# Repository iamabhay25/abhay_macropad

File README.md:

<div align="center">

# Abhay's Macropad

### Custom 9-Key Macropad

Custom designed macropad for everyday use.

Features 9 keys with per-key underglow LEDs, a 128×32 SSD1306 OLED display, and a rotary encoder.

<br><br>

<br><br>

| ⚡ RP2040 MC | ⌨️ 9 Keys | ✨ Underlit Keys | 📺 .91" OLED Screen | 🎛️ 1 Rotary Encoder |
|:--:|:--:|:--:|:--:|:--:|

</div>

<br><br><br><br>

<div align="center">

### Sponsored By

<br>

</div>

<br><br><br><br><br>

<div align="center">

### Bill of Materials

<br>

<div align="center">

| Qty | Component | Cost |
|:---:|-----------|------|
| 4x | [M2.5 Self-Tapping Screws](https://www.aliexpress.us/item/3256805544601650.html) | $1.97 |
| 4x | [M3 Heat-Set Inserts](https://www.aliexpress.us/item/3256808480358197.html) | $1.99 |
| 4x | [M3 Machine Screws](https://www.aliexpress.us/item/2255800784679048.html) | $1.87 |
| 1x | [Seeed Studio XIAO RP2040](https://www.aliexpress.us/item/3256807240972277.html) | $11.73 |
| 1x | [SSD1306 128×32 OLED Display](https://www.aliexpress.us/item/3256805115814136.html) | $2.39 |
| 9x | [Tactile Switches](https://www.aliexpress.us/item/3256808352947766.html) | $3.51 |
| 9x | [Blank White Keycaps](https://www.aliexpress.us/item/3256809017491500.html) | $3.25 |
| 9x | [SOD-123 Diodes](https://www.aliexpress.us/item/3256805388348871.html) | $1.53 |
| 3x | [1206 Capacitors](https://www.aliexpress.us/item/3256807177349573.html) | $1.27 |
| 1x | [0805 Resistor](https://www.aliexpress.us/item/3256809618872827.html) | $1.42 |
| 1x | [Bus Buffer Gate](https://www.aliexpress.us/item/3256807066238250.html) | $1.51 |
| 1x | [Soldering Wire](https://www.aliexpress.us/item/3256806675545472.html) | $1.41 |
| 1x | [Custom PCB](https://jlcpcb.com/) | $3.30 |
| 1x | 3D Printed Case (Printing Legion) | $0.00 |

<br>

**Parts Subtotal:** $35.16

**Fees:** $4.01

**Tax:** $2.96

**Printing Legion Shipping:** $7.00

**Grand Total:** $49.13

<br><br><br><br><br>

<div align="left">
  
### PCB Schematic

<br>

<br><br>

### PCB Layout

<br>

<div align="center">

**Top Layer**

<br>

<br><br>

**Bottom Layer**

<br>

<br><br>

**3D View**

<br>

<br><br>

</div>

<br><br>

### Case Design

<br>

<div align="center">

**Top Case**

<br>

<br><br>

**Bottom Case**

<br>

</div>

<br><br>

### Final Assembly

<br>

<div align="center">

</div>

<br><br>

<div align="center">

*Designed and Built by Abhay P.*

</div>

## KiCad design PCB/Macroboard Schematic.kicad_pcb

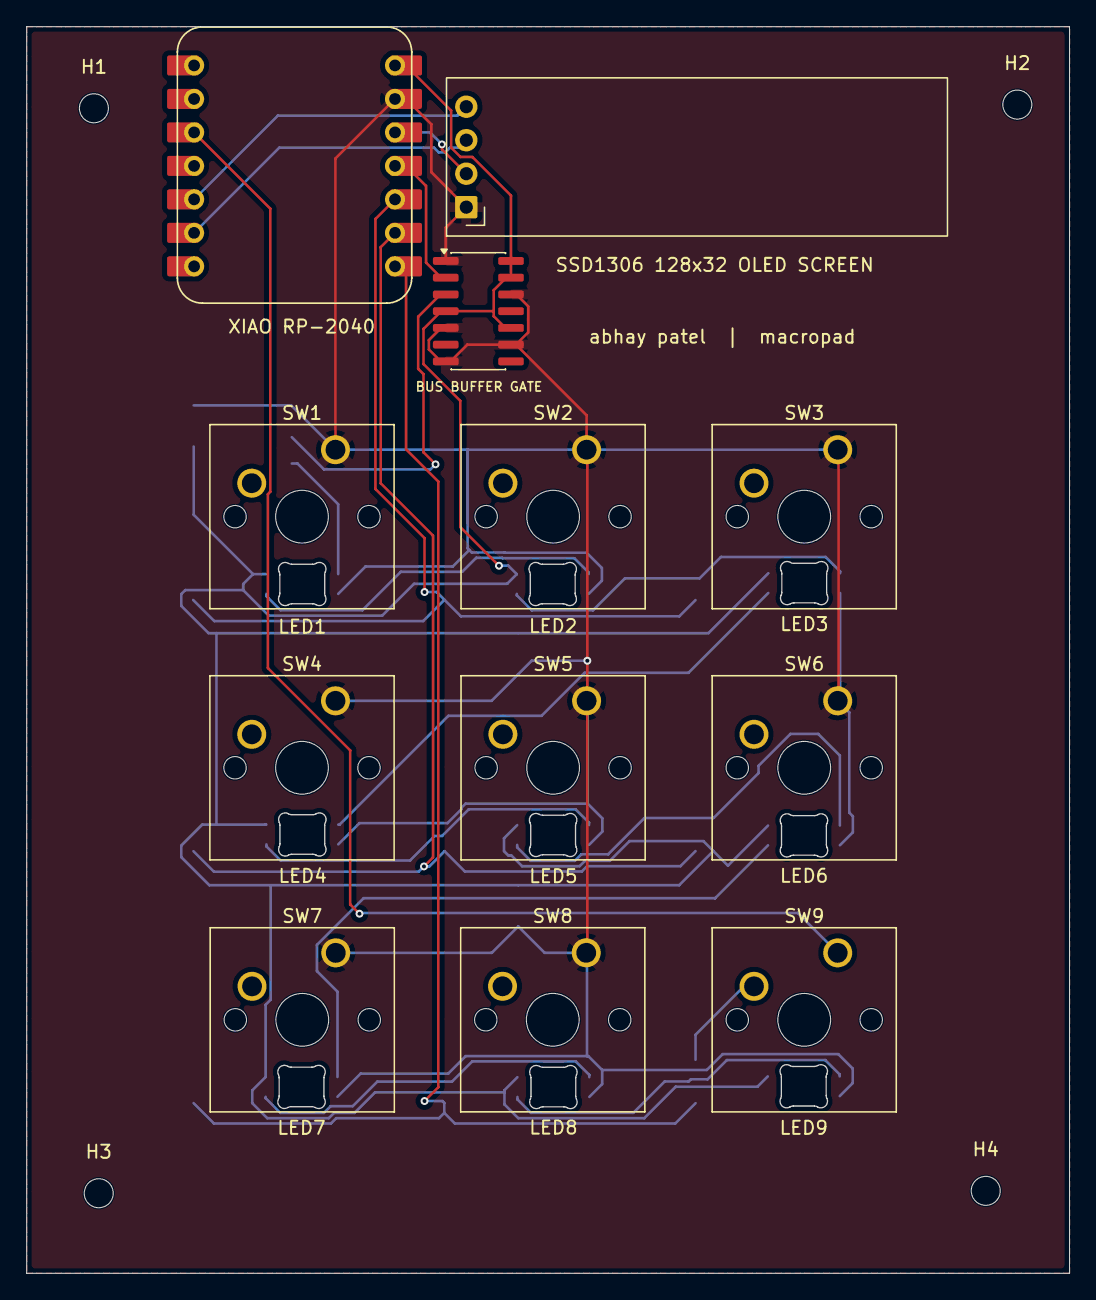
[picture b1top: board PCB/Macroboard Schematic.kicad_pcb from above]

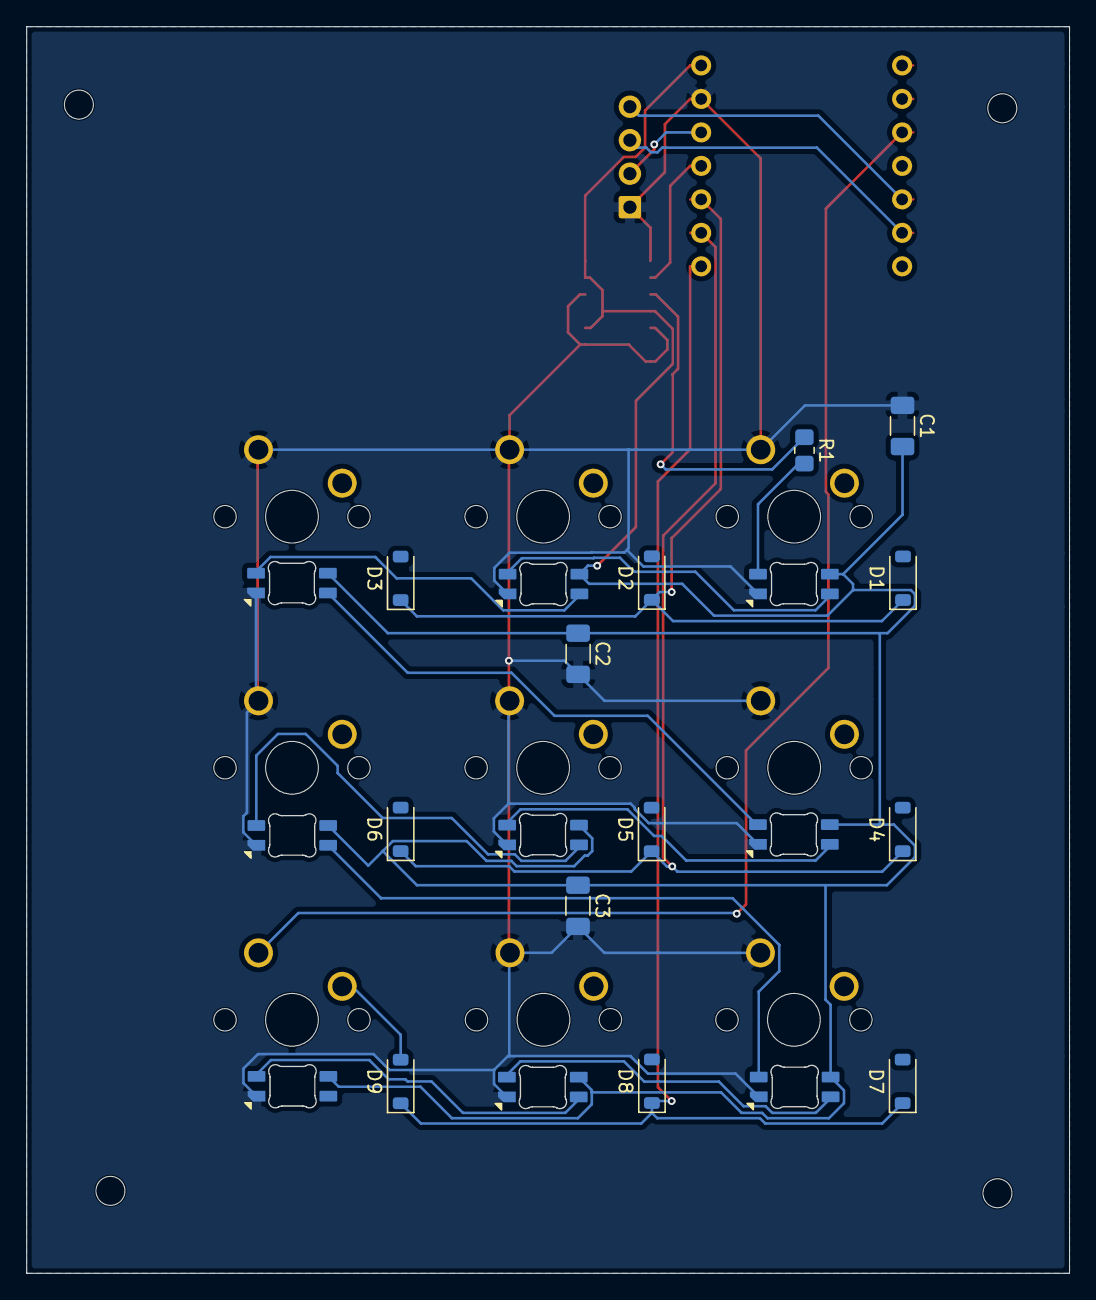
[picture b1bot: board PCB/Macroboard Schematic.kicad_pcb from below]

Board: 2 copper layers, 79.1 x 94.6 mm, 38 parts (22 on the bottom side), 21 nets.

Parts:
BUS BUFFER GATE: 74AHCT125; SOIC-14_3.9x8.7mm_P1.27mm
C1, C2, C3: 100nF; C_1206_3216Metric_Pad1.33x1.80mm_HandSolder
D1, D2, D3, D4, D5, D6, D7, D8, D9: 1N4148W; D_SOD-123
H1, H2, H3, H4: MountingHole; MountingHole_2.2mm_M2
LED1, LED2, LED3, LED4, LED5, LED6, LED7, LED8, LED9: MX_SK6812MINI-E; LED_MX_6028R
R1: 330R; R_0805_2012Metric_Pad1.20x1.40mm_HandSolder
SSD1306 128x32 OLED SCREEN: ER_OLEDM0.91_1x-I2C
SW1, SW2, SW3, SW4, SW5, SW6, SW7, SW8, SW9: SW_Push; SW_Cherry_MX_1.00u_PCB
U3: XIAO-RP2040-DIP

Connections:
+3.3V: SSD1306 128x32 OLED SCREEN.2 (VCC), U3.12 (3V3)
+5V: BUS BUFFER GATE.4, BUS BUFFER GATE.10, BUS BUFFER GATE.13, BUS BUFFER GATE.14 (VCC), C1.2, C2.1, C3.1, LED1.1 (VDD), LED2.1 (VDD), LED3.1 (VDD), LED4.1 (VDD), LED5.1 (VDD), LED6.1 (VDD), LED7.1 (VDD), LED8.1 (VDD), LED9.1 (VDD), U3.14 (VBUS)
COLUMN 3: SW9.1, U3.3 (P28_A2_D2)
GND: BUS BUFFER GATE.1, BUS BUFFER GATE.5, BUS BUFFER GATE.7 (GND), BUS BUFFER GATE.9, BUS BUFFER GATE.12, C1.1, C2.2, C3.2, LED1.3 (VSS), LED2.3 (VSS), LED3.3 (VSS), LED4.3 (VSS), LED5.3 (VSS), LED6.3 (VSS), LED7.3 (VSS), LED8.3 (VSS), LED9.3 (VSS), SSD1306 128x32 OLED SCREEN.1 (GND), SW1.1, SW2.1, SW3.1, SW4.1, SW5.1, SW6.1, SW7.1, SW8.1, U3.13 (GND)
LED: BUS BUFFER GATE.2, U3.11 (P3_D10_MOSI)
unnamed: D9.2 (A), SW9.2
unnamed: LED1.4 (DIN), R1.2
unnamed: LED1.2 (DOUT), LED2.4 (DIN)
unnamed: LED2.2 (DOUT), LED3.4 (DIN)
unnamed: LED3.2 (DOUT), LED4.4 (DIN)
unnamed: LED4.2 (DOUT), LED5.4 (DIN)
unnamed: LED5.2 (DOUT), LED6.4 (DIN)
unnamed: LED6.2 (DOUT), LED7.4 (DIN)
unnamed: LED7.2 (DOUT), LED8.4 (DIN)
unnamed: LED8.2 (DOUT), LED9.4 (DIN)
unnamed: BUS BUFFER GATE.3, R1.1
ROW 1: D1.1 (K), D2.1 (K), D3.1 (K), U3.10 (P4_D9_MISO)
ROW 2: D4.1 (K), D5.1 (K), D6.1 (K), U3.9 (P2_D8_SCK)
ROW 3: D7.1 (K), D8.1 (K), D9.1 (K), U3.8 (P1_D7_RX)
SCL: SSD1306 128x32 OLED SCREEN.3 (SCL), U3.6 (P7_SCL_D5)
SDA: SSD1306 128x32 OLED SCREEN.4 (SDA), U3.5 (P6_SDA_D4)

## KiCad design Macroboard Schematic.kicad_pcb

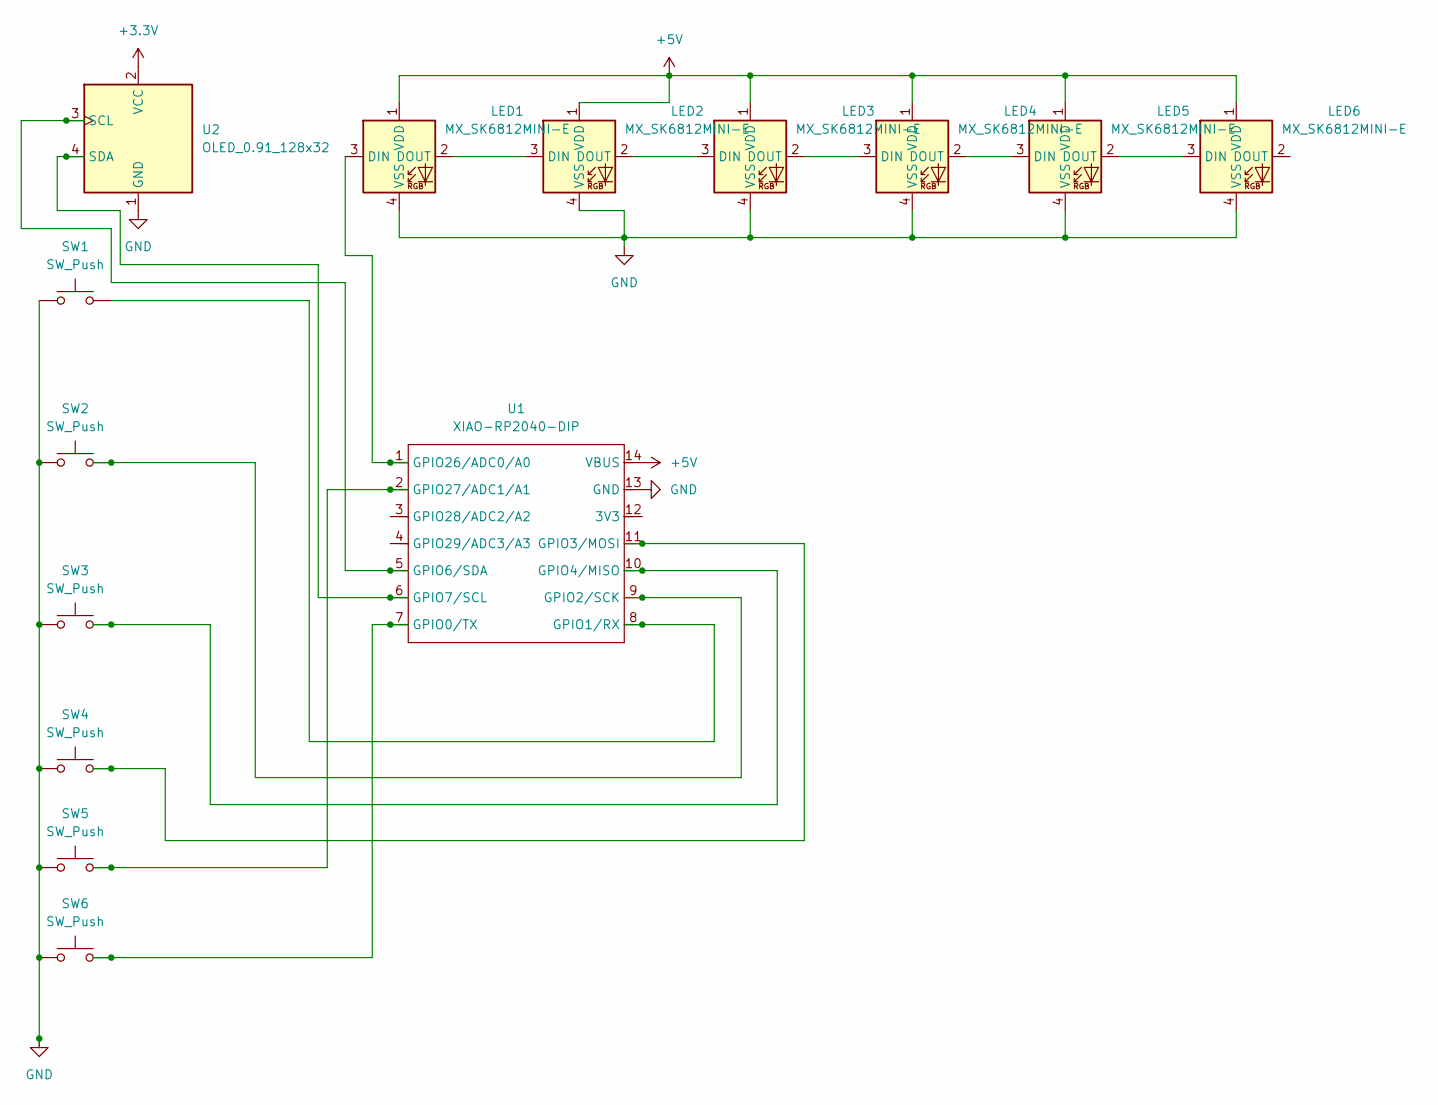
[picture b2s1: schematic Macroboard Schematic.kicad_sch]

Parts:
LED1, LED2, LED3, LED4, LED5, LED6: MX_SK6812MINI-E; LED_SK6812MINI-E_3.2x2.8mm_P1.5mm_ReverseMount
SW1, SW2, SW3, SW4, SW5, SW6: SW_Push; SW_Cherry_MX_1.00u_PCB
U1: XIAO-RP2040-DIP
U2: OLED_0.91_128x32

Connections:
+3.3V: U2.2 (VCC)
+5V: LED1.1 (VDD), LED2.1 (VDD), LED3.1 (VDD), LED4.1 (VDD), LED5.1 (VDD), LED6.1 (VDD), U1.14 (VBUS)
GND: LED1.4 (VSS), LED2.4 (VSS), LED3.4 (VSS), LED4.4 (VSS), LED5.4 (VSS), LED6.4 (VSS), SW1.1, SW2.1, SW3.1, SW4.1, SW5.1, SW6.1, U1.13 (GND), U2.1 (GND)
unnamed: LED1.3 (DIN), U1.1 (GPIO26/ADC0/A0)
unnamed: LED1.2 (DOUT), LED2.3 (DIN)
unnamed: LED2.2 (DOUT), LED3.3 (DIN)
unnamed: LED3.2 (DOUT), LED4.3 (DIN)
unnamed: LED4.2 (DOUT), LED5.3 (DIN)
unnamed: LED5.2 (DOUT), LED6.3 (DIN)
unnamed: SW6.2, U1.7 (GPIO0/TX)
unnamed: SW1.2, U1.8 (GPIO1/RX)
unnamed: SW2.2, U1.9 (GPIO2/SCK)
unnamed: SW4.2, U1.11 (GPIO3/MOSI)
unnamed: SW3.2, U1.10 (GPIO4/MISO)
unnamed: U1.5 (GPIO6/SDA), U2.3 (SCL)
unnamed: U1.6 (GPIO7/SCL), U2.4 (SDA)
unnamed: SW5.2, U1.2 (GPIO27/ADC1/A1)

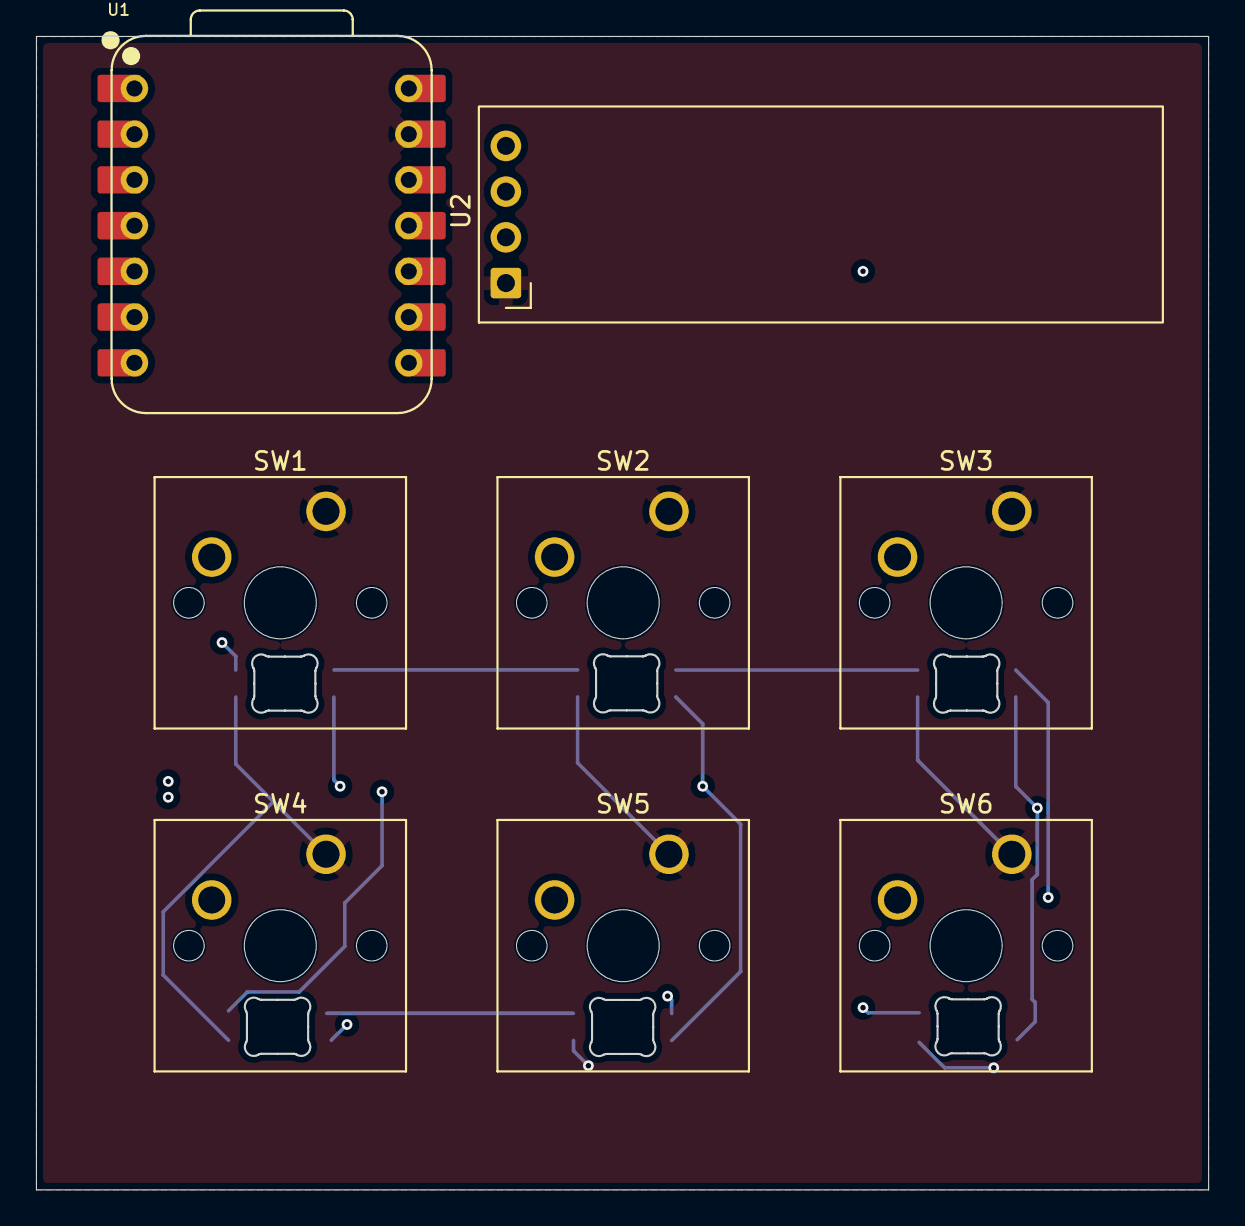
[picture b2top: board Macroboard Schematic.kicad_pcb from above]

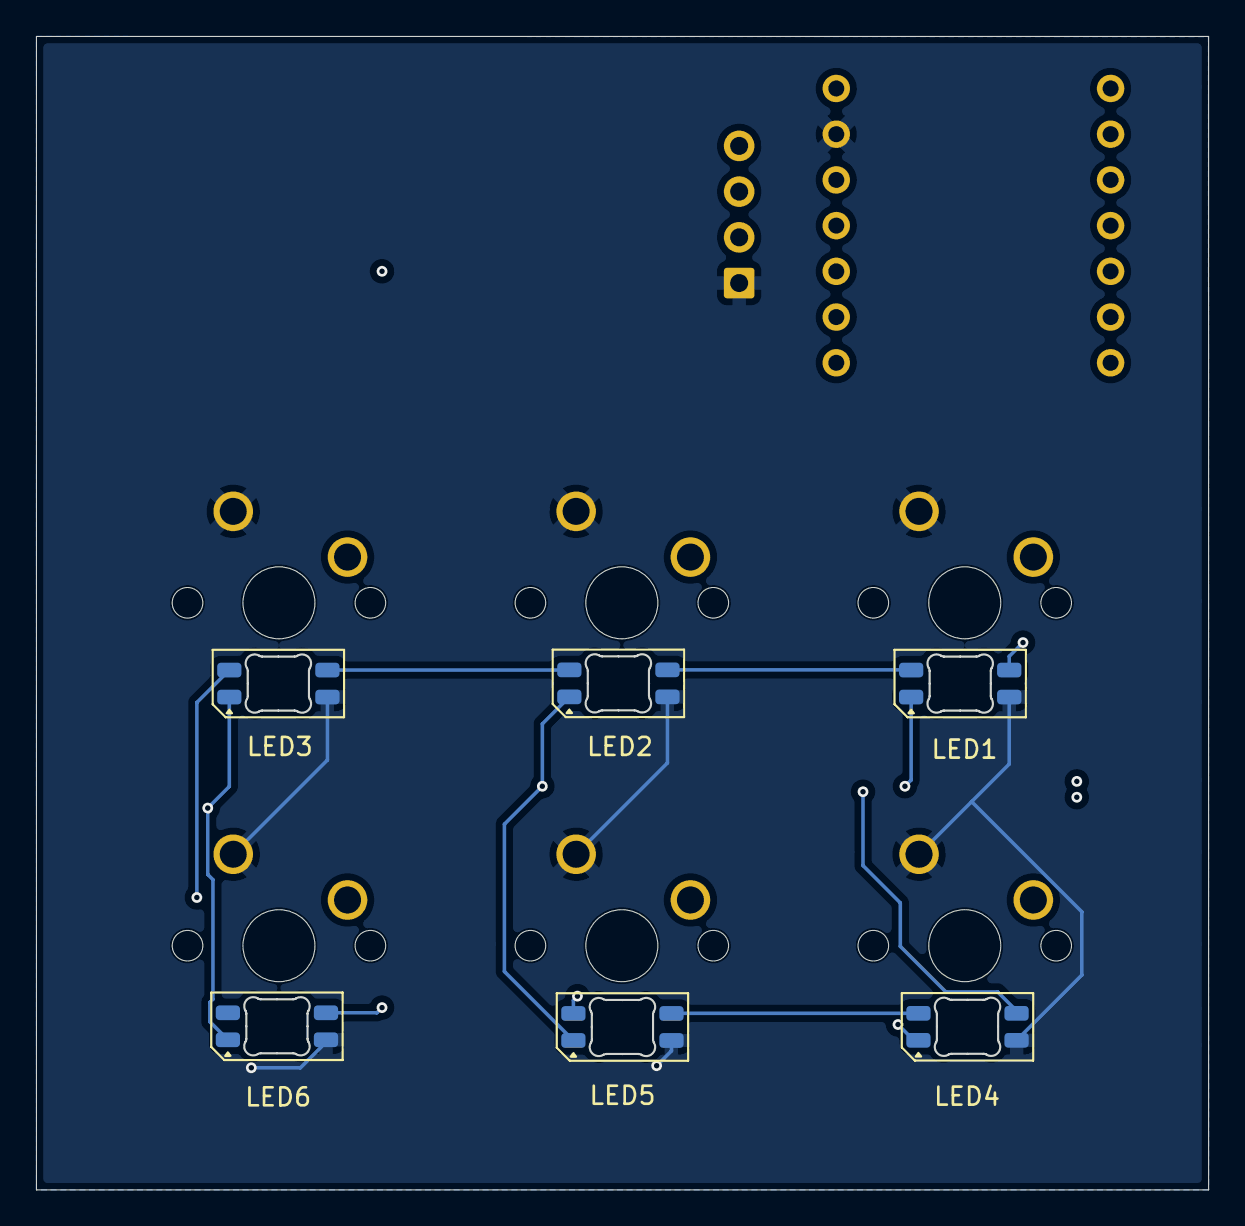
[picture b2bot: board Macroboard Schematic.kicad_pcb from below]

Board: 4 copper layers, 65.1 x 64.1 mm, 14 parts (6 on the bottom side), 16 nets.

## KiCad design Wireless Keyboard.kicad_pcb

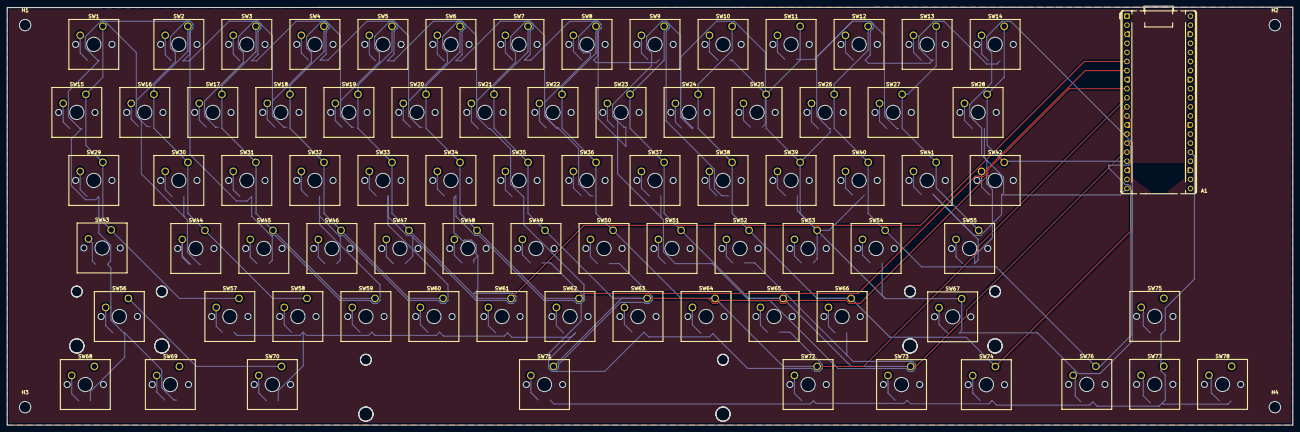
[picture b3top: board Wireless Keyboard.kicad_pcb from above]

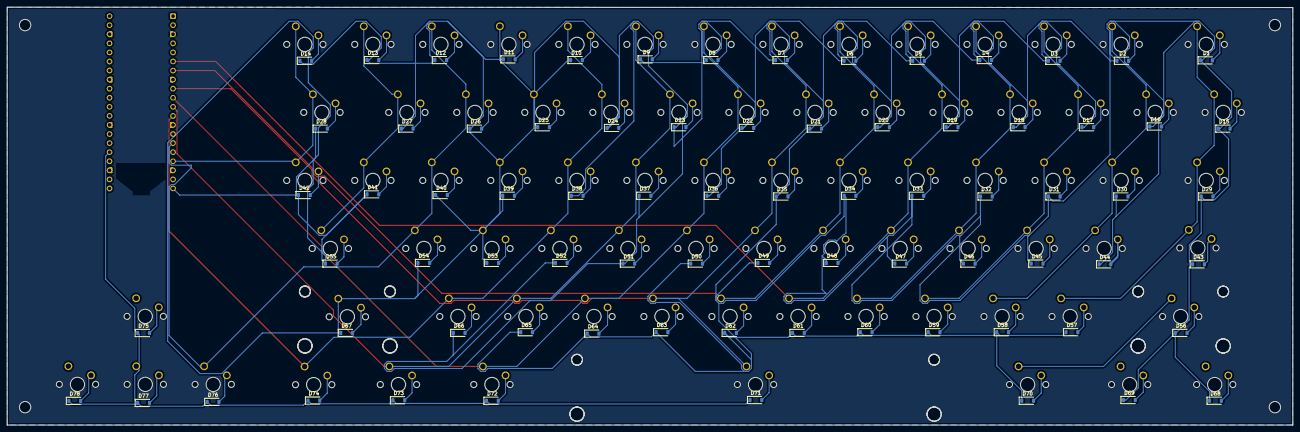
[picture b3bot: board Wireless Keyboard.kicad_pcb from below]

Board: 4 copper layers, 360.0 x 117.0 mm, 164 parts (78 on the bottom side), 93 nets.

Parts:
A1: SC0918; RaspberryPi_Pico_Common_THT
D1, D2, D3, D4, D5, D6, D7, D8, D9, D10, D11, D12, D13, D14, D15, D16, D17, D18, D19, D20, D21, D22, D23, D24, D25, D26, D27, D28, D29, D30, D31, D32, D33, D34, D35, D36, D37, D38, D39, D40, D41, D42, D43, D44, D45, D46, D47, D48, D49, D50, D51, D52, D53, D54, D55, D56, D57, D58, D59, D60, D61, D62, D63, D64, D65, D66, D67, D68, D69, D70, D71, D72, D73, D74, D75, D76, D77, D78: D; D_SOD-123
H1, H2, H3, H4: MountingHole; MountingHole_3.2mm_M3
S3, S4: MX_stab; STAB_MX_2.25u
S5: MX_stab; STAB_MX_6.25u
SW1, SW28, SW29, SW72: SW_Push; SW_Cherry_MX_1.50u_PCB
SW2, SW3, SW4, SW5, SW6, SW7, SW8, SW9, SW10, SW11, SW12, SW13, SW14, SW15, SW16, SW17, SW18, SW19, SW20, SW21, SW22, SW23, SW24, SW25, SW26, SW27, SW30, SW31, SW32, SW33, SW34, SW35, SW36, SW37, SW38, SW39, SW40, SW41, SW42, SW44, SW45, SW46, SW47, SW48, SW49, SW50, SW51, SW52, SW53, SW54, SW57, SW58, SW59, SW60, SW61, SW62, SW63, SW64, SW65, SW66, SW75, SW76, SW77, SW78: SW_Push; SW_Cherry_MX_1.00u_PCB
SW43, SW55, SW70: SW_Push; SW_Cherry_MX_1.75u_PCB
SW56, SW67: SW_Push; SW_Cherry_MX_2.25u_PCB
SW68, SW69, SW73, SW74: SW_Push; SW_Cherry_MX_1.25u_PCB
SW71: SW_Push; SW_Cherry_MX_6.25u_PCB

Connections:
/column 1: A1.1 (GP0), SW1.1, SW15.1, SW29.1, SW43.1, SW57.1
/column 2: A1.2 (GP1), SW2.1, SW16.1, SW30.1, SW44.1, SW58.1
/column 3: A1.4 (GP2), SW3.1, SW17.1, SW31.1, SW45.1, SW59.1
/column 4: A1.5 (GP3), SW4.1, SW18.1, SW32.1, SW46.1, SW60.1
/column 5: A1.6 (GP4), SW5.1, SW19.1, SW33.1, SW47.1, SW61.1
/column 6: A1.7 (GP5), SW6.1, SW20.1, SW34.1, SW48.1, SW62.1
/column 7: A1.9 (GP6), SW7.1, SW21.1, SW35.1, SW49.1, SW63.1, SW71.1
/column 8: A1.10 (GP7), SW8.1, SW22.1, SW36.1, SW50.1, SW64.1, SW72.1
/column 9: A1.11 (GP8), SW9.1, SW23.1, SW37.1, SW51.1, SW65.1, SW73.1
/column 10: A1.12 (GP9), SW10.1, SW24.1, SW38.1, SW52.1, SW66.1, SW74.1
/column 11: A1.14 (GP10), A1.19 (GP14), A1.20 (GP15), A1.21 (GP16), A1.22 (GP17), A1.24 (GP18), D1.1 (K), D2.1 (K), D3.1 (K), D4.1 (K), D5.1 (K), D6.1 (K), D7.1 (K), D8.1 (K), D9.1 (K), D10.1 (K), D11.1 (K), D12.1 (K), D13.1 (K), D14.1 (K), D15.1 (K), D16.1 (K), D17.1 (K), D18.1 (K), D19.1 (K), D20.1 (K), D21.1 (K), D22.1 (K), D23.1 (K), D24.1 (K), D25.1 (K), D26.1 (K), D27.1 (K), D28.1 (K), D29.1 (K), D30.1 (K), D31.1 (K), D32.1 (K), D33.1 (K), D34.1 (K), D35.1 (K), D36.1 (K), D37.1 (K), D38.1 (K), D39.1 (K), D40.1 (K), D41.1 (K), D42.1 (K), D43.1 (K), D44.1 (K), D45.1 (K), D46.1 (K), D47.1 (K), D48.1 (K), D49.1 (K), D50.1 (K), D51.1 (K), D52.1 (K), D53.1 (K), D54.1 (K), D55.1 (K), D56.1 (K), D57.1 (K), D58.1 (K), D59.1 (K), D60.1 (K), D61.1 (K), D62.1 (K), D63.1 (K), D64.1 (K), D65.1 (K), D66.1 (K), D67.1 (K), D68.1 (K), D69.1 (K), D70.1 (K), SW11.1, SW25.1, SW39.1, SW53.1, SW67.1, SW75.1
/column 12: A1.15 (GP11), SW12.1, SW26.1, SW40.1, SW54.1, SW68.1, SW76.1
/column 13: A1.16 (GP12), SW13.1, SW27.1, SW41.1, SW55.1, SW69.1, SW77.1
/column 14: A1.17 (GP13), SW14.1, SW28.1, SW42.1, SW56.1, SW70.1, SW78.1
/row 6: A1.25 (GP19), D71.1 (K), D72.1 (K), D73.1 (K), D74.1 (K), D75.1 (K), D76.1 (K), D77.1 (K), D78.1 (K)
unnamed: D1.2 (A), SW1.2
unnamed: D2.2 (A), SW2.2
unnamed: D3.2 (A), SW3.2
unnamed: D4.2 (A), SW4.2
unnamed: D5.2 (A), SW5.2
unnamed: D6.2 (A), SW6.2
unnamed: D7.2 (A), SW7.2
unnamed: D8.2 (A), SW8.2
unnamed: D9.2 (A), SW9.2
unnamed: D10.2 (A), SW10.2
unnamed: D11.2 (A), SW11.2
unnamed: D12.2 (A), SW12.2
unnamed: D13.2 (A), SW13.2
unnamed: D14.2 (A), SW14.2
unnamed: D15.2 (A), SW15.2
unnamed: D16.2 (A), SW16.2
unnamed: D17.2 (A), SW17.2
unnamed: D18.2 (A), SW18.2
unnamed: D19.2 (A), SW19.2
unnamed: D20.2 (A), SW20.2
unnamed: D21.2 (A), SW21.2
unnamed: D22.2 (A), SW22.2
unnamed: D23.2 (A), SW23.2
unnamed: D24.2 (A), SW24.2
unnamed: D25.2 (A), SW25.2
unnamed: D26.2 (A), SW26.2
unnamed: D27.2 (A), SW27.2
unnamed: D28.2 (A), SW28.2
unnamed: D29.2 (A), SW29.2
unnamed: D30.2 (A), SW30.2
unnamed: D31.2 (A), SW31.2
unnamed: D32.2 (A), SW32.2
unnamed: D33.2 (A), SW33.2
unnamed: D34.2 (A), SW34.2
unnamed: D35.2 (A), SW35.2
unnamed: D36.2 (A), SW36.2
unnamed: D37.2 (A), SW37.2
unnamed: D38.2 (A), SW38.2
unnamed: D39.2 (A), SW39.2
unnamed: D40.2 (A), SW40.2
unnamed: D41.2 (A), SW41.2
unnamed: D42.2 (A), SW42.2
unnamed: D43.2 (A), SW43.2
unnamed: D44.2 (A), SW44.2
unnamed: D45.2 (A), SW45.2
unnamed: D46.2 (A), SW46.2
unnamed: D47.2 (A), SW47.2
unnamed: D48.2 (A), SW48.2
unnamed: D49.2 (A), SW49.2
unnamed: D50.2 (A), SW50.2
unnamed: D51.2 (A), SW51.2
unnamed: D52.2 (A), SW52.2
unnamed: D53.2 (A), SW53.2
unnamed: D54.2 (A), SW54.2
unnamed: D55.2 (A), SW55.2
unnamed: D56.2 (A), SW56.2
unnamed: D57.2 (A), SW57.2
unnamed: D58.2 (A), SW58.2
unnamed: D59.2 (A), SW59.2
unnamed: D60.2 (A), SW60.2
unnamed: D61.2 (A), SW61.2
unnamed: D62.2 (A), SW62.2
unnamed: D63.2 (A), SW63.2
unnamed: D64.2 (A), SW64.2
unnamed: D65.2 (A), SW65.2
unnamed: D66.2 (A), SW66.2
unnamed: D67.2 (A), SW67.2
unnamed: D68.2 (A), SW68.2
unnamed: D69.2 (A), SW69.2
unnamed: D70.2 (A), SW70.2
unnamed: D71.2 (A), SW71.2
unnamed: D72.2 (A), SW72.2
unnamed: D73.2 (A), SW73.2
unnamed: D74.2 (A), SW74.2
unnamed: D75.2 (A), SW75.2
unnamed: D76.2 (A), SW76.2
unnamed: D77.2 (A), SW77.2
unnamed: D78.2 (A), SW78.2

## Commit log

2026-02-01 Rename Macroboard Schematic.kicad_pcb to PCB/Macroboard Schematic.kicad_pcb
2026-02-01 Rename Macroboard Schematic.kicad_pro to PCB/Macroboard Schematic.kicad_pro
2026-02-01 Rename Macroboard Schematic.kicad_sch to PCB/Macroboard Schematic.kicad_sch
2026-02-06 updating to current cad files
2026-02-06 updated to current stp files
2026-02-10 Refactor key macros and add tap dance functionality
2026-02-10 Implement LED blinking functions with threading
    Added LED blinking functionality with threading support.
2026-03-23 Update README with additional images and BOM
2026-03-23 Update README.md with additional line breaks
2026-03-23 Rename Wireless Keyboard.kicad_pcb to PCB/Wireless Keyboard.kicad_pcb
2026-03-23 Rename Wireless Keyboard.kicad_pro to PCB/Wireless Keyboard.kicad_pro
2026-04-18 Modify BOM and update macroboard images
    Updated the Bill of Materials and replaced images for the macroboard assembly.
2026-04-18 Rename Abhay Macroboard Top.step to CAD/Abhay Macroboard Top.step
2026-04-18 Rename Abhay's Macropad Bottom.step to CAD/Abhay's Macropad Bottom.step
2026-04-18 Rename macroboard assembly.f3z to ASSEMBLY/macroboard assembly.f3z
2026-04-18 Rename abhaymacroboardfirmware.py to FIRMWARE/abhaymacroboardfirmware.py
2026-05-22 Rename MACROPAD BOTTOM CASE.step to CAD/MACROPAD BOTTOM CASE.step
2026-05-22 Rename MACROPAD TOP CASE.step to CAD/MACROPAD TOP CASE.step
2026-05-30 Revise README for Abhay's Macropad
    Updated README to reflect new features and design details.
2026-05-30 Update README to specify individual underlit keys
2026-05-31 Add TapDance and Macros modules with new macros
2026-05-31 Rename abhaymacroboardfirmware.py to macroboardfirmware.py
2026-05-31 Update print statement from 'Hello' to 'Goodbye'
2026-06-01 Rename macroboard assembly.f3z to macroboard_assembly.f3z
2026-06-01 Rename GBR_DRILL_FILES/ macropad_gbr_drl_files.zip to MACROPAD GBR AND DRL FILES macropad_gbr_drl_files.zip
2026-06-01 Rename Macroboard Schematic.kicad_pcb to Macroboard Schematic.kicad_pcb
2026-06-01 Rename Macroboard Schematic.kicad_pro to Macroboard Schematic.kicad_pro
2026-06-01 Rename ASSEMBLY/macroboard_assembly.f3z to 2_CAD FILES/ASSEMBLY/macroboard_assembly.f3z
2026-06-01 Rename macropad_firmware_documentation.md to macropad_firmware_documentation.md
2026-06-01 Rename macropadfirmware.py to macropadfirmware.py
